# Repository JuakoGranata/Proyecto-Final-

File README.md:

# Proyecto-Final-
Proyecto Final Miragüa - Granata Joaquin, lorenzo Fernandez, Selene Ramirez, Matias Caram y Bautista Paz - 5° 2° Avionica - https://github.com/JuakoGranata/Proyecto-Final-/blob/main/Mirag%C3%BCa-Pagina_Web/index.html

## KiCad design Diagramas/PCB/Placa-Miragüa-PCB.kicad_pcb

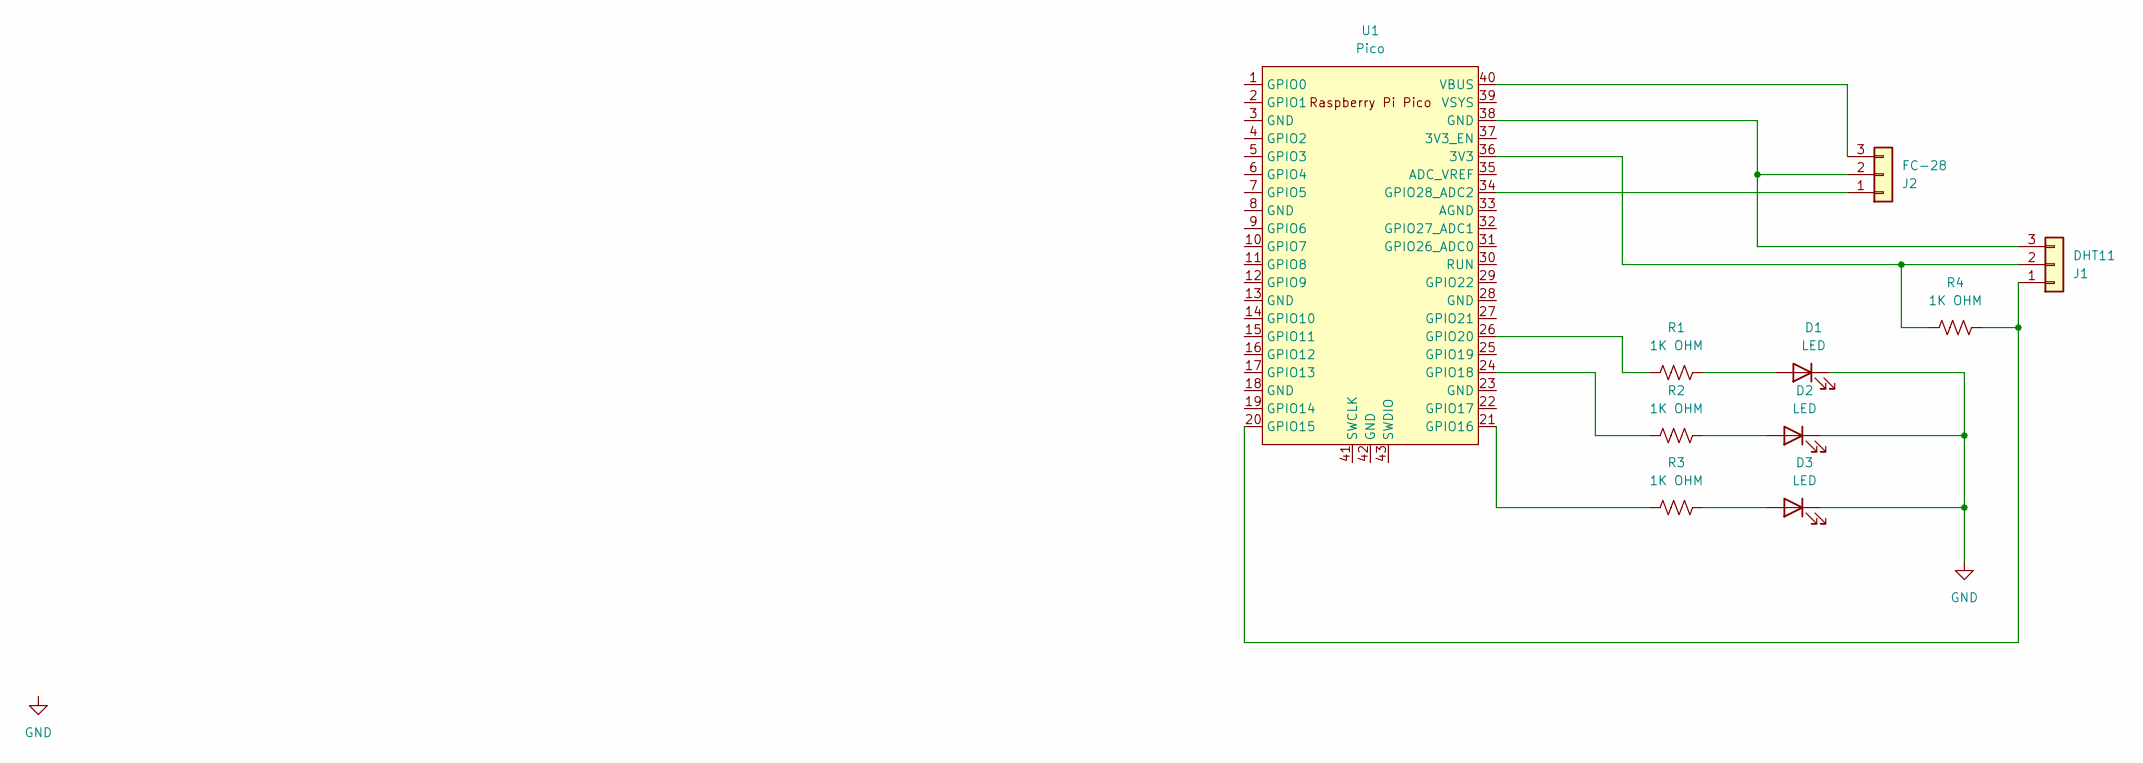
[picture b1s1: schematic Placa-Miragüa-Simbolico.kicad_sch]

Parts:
D1, D2, D3: LED; LED_1210_3225Metric_Pad1.42x2.65mm_HandSolder
J1: DHT11; TerminalBlock_bornier-3_P5.08mm
J2: FC-28; TerminalBlock_bornier-3_P5.08mm
R1, R2, R3, R4: 1K OHM; R_1206_3216Metric_Pad1.30x1.75mm_HandSolder
U1: Pico; RPi_Pico_SMD_TH

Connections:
GND: D1.1 (K), D2.1 (K), D3.1 (K), U1.19 (GPIO14), U1.22 (GPIO17), U1.23 (GND), U1.25 (GPIO19), U1.27 (GPIO21), U1.28 (GND), U1.29 (GPIO22), U1.30 (RUN), U1.31 (GPIO26_ADC0), U1.32 (GPIO27_ADC1), U1.33 (AGND), U1.35 (ADC_VREF), U1.37 (3V3_EN), U1.39 (VSYS), U1.41 (SWCLK), U1.42 (GND), U1.43 (SWDIO)
unnamed: D1.2 (A), R1.1
unnamed: D2.2 (A), R2.1
unnamed: D3.2 (A), R3.1
unnamed: J1.1, R4.1, U1.20 (GPIO15)
unnamed: J1.2, R4.2, U1.36 (3V3)
unnamed: J1.3, J2.2, U1.38 (GND)
unnamed: J2.1, U1.34 (GPIO28_ADC2)
unnamed: J2.3, U1.40 (VBUS)
unnamed: R3.2, U1.21 (GPIO16)
unnamed: R2.2, U1.24 (GPIO18)
unnamed: R1.2, U1.26 (GPIO20)

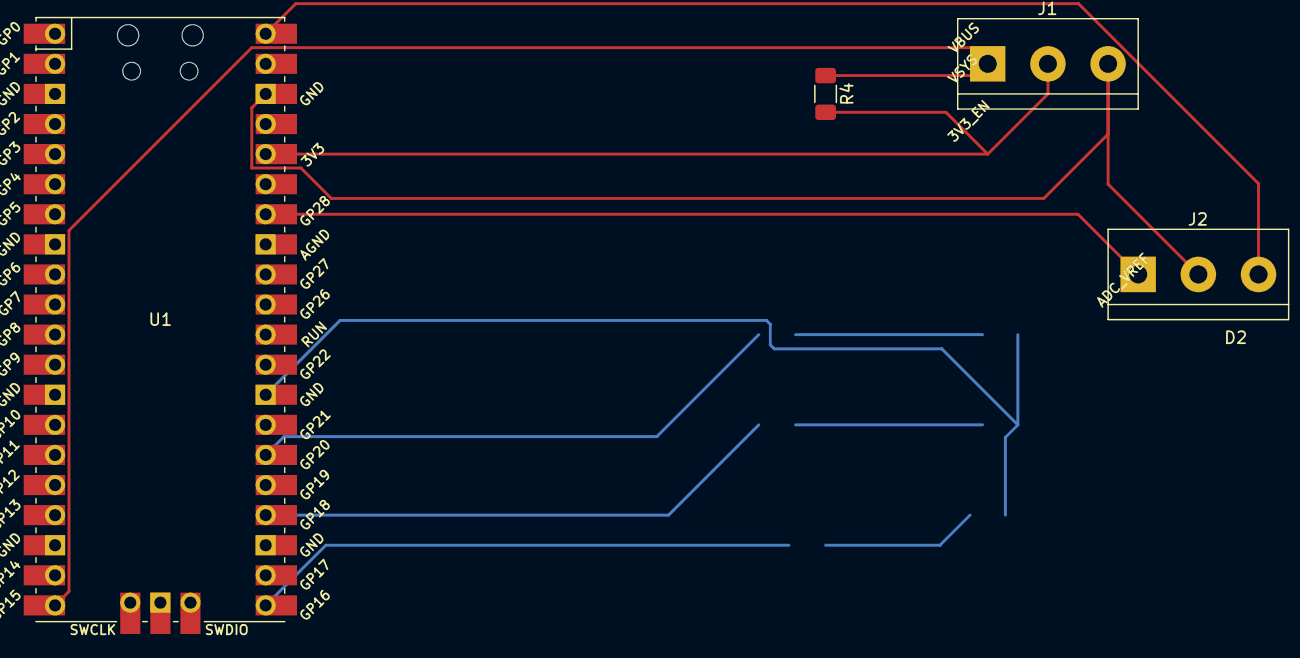
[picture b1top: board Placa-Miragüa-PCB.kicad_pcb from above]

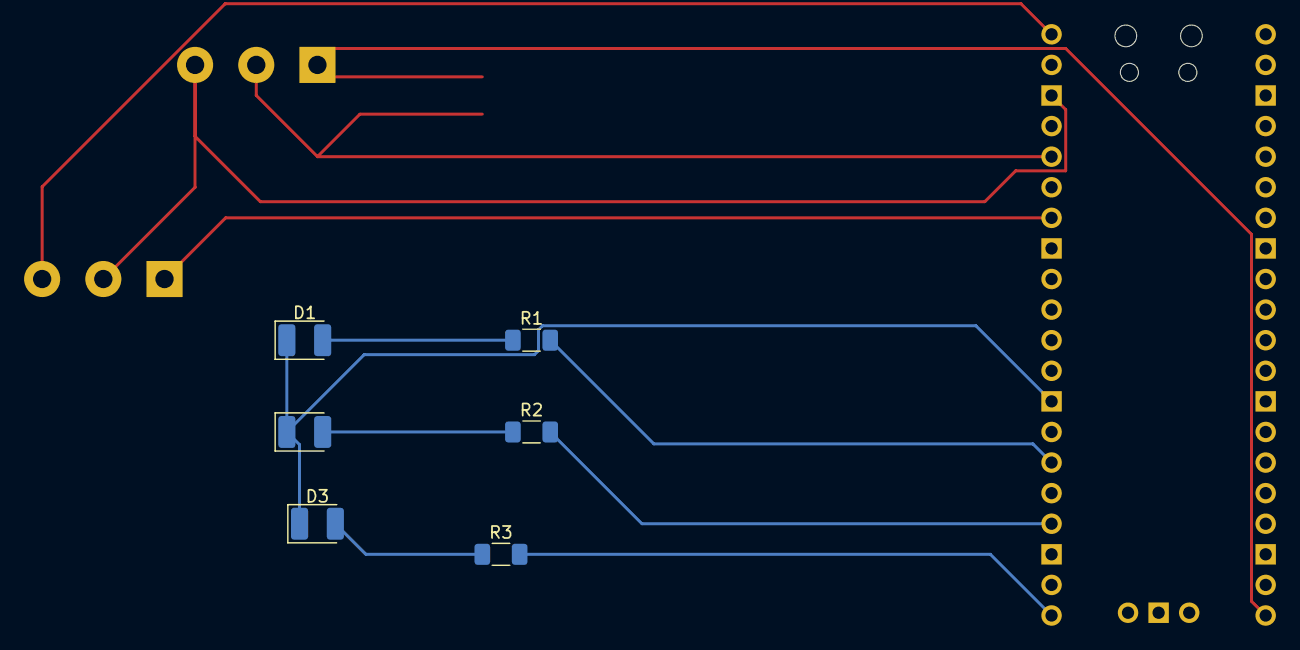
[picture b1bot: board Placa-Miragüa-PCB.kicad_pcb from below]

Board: 2 copper layers, 10 parts (6 on the bottom side), 12 nets.
